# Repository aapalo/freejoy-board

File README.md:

# Freejoy input board

Features:
- Inputs for eg two encoders, eight axes and six shift registers
- Several boards can be daisy-chained via the 1x5 pin socket J103.
- Meant to be used with the Freejoy software: <https://github.com/FreeJoy-Team/FreeJoy>
----

The required components include:
- STM32F103 "Blue Pill"
- Shift register, 74HC165N, DIP-16
- SMD resistors, 10k Ohm, 0805
- SMD capacitors, 470nF, 0805
- Pin sockets and/or headers, 2.54mm pitch
- Buttons/switches
- Jumper wires for the buttons/switches

----

[//]: # (Todo: add pictures of a soldered version)

The schematic (see also pics/schema.pdf):

Top side, with the 3d view and layout view:

Bottom side, with the 3d view and layout view:

Both the top and bottom layer visible:

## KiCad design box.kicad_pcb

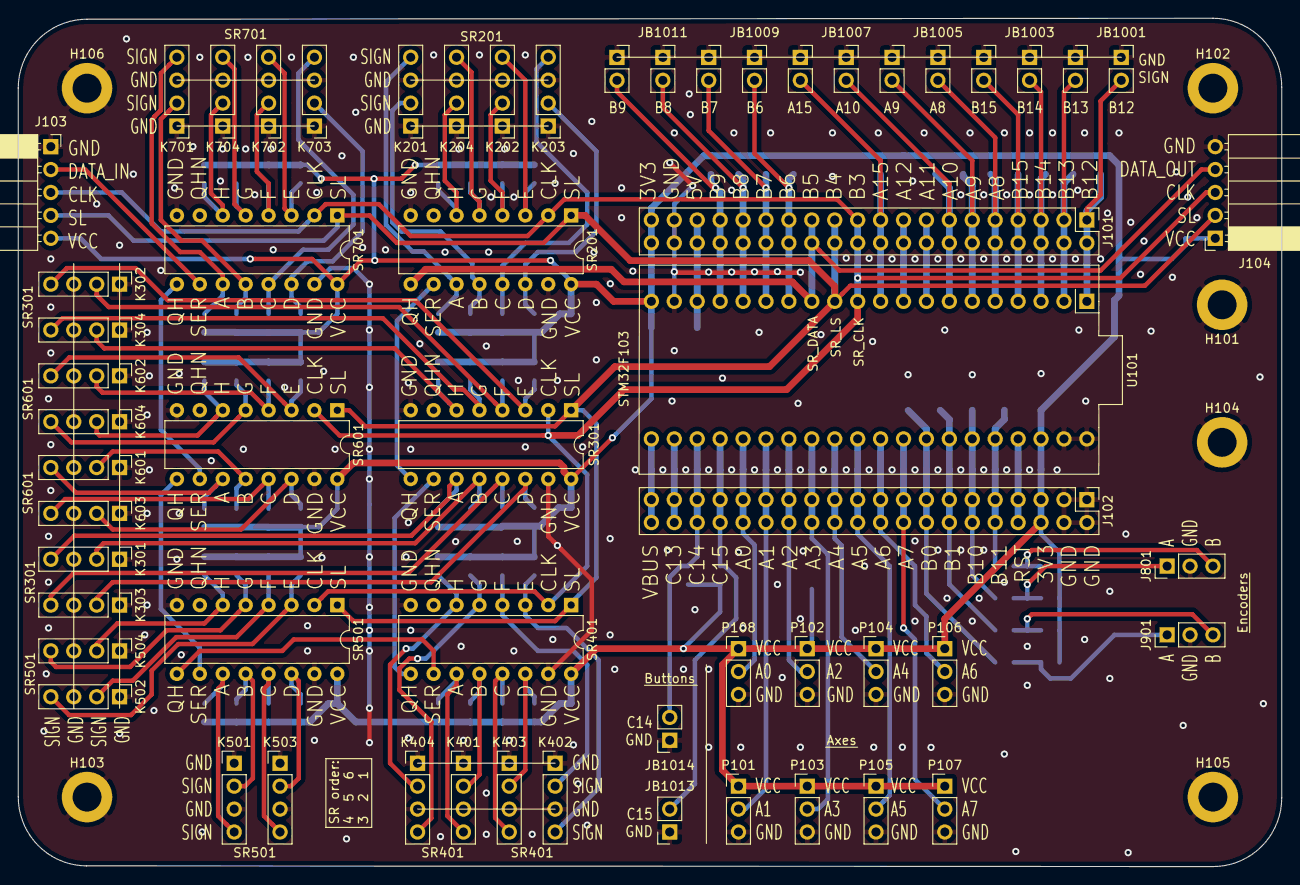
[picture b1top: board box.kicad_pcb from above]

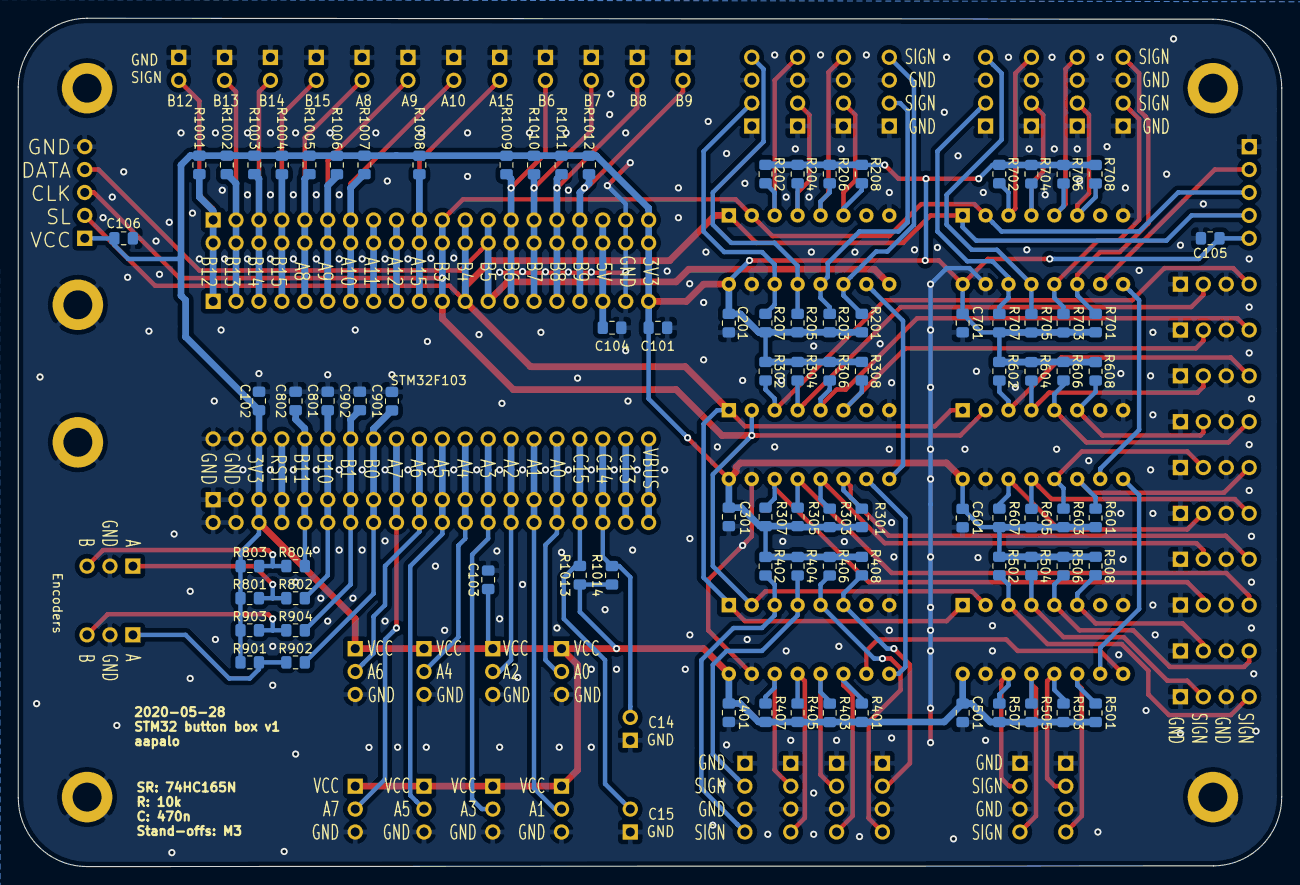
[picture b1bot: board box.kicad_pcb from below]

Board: 2 copper layers, 140.0 x 94.0 mm, 151 parts (86 on the bottom side), 95 nets.

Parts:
C101, C102, C103, C104, C105, C106, C201, C301, C401, C501, C601, C701: 470n; C_0805_2012Metric_Pad1.15x1.40mm_HandSolder
C801, C802, C901, C902: 10n; C_0805_2012Metric_Pad1.15x1.40mm_HandSolder
H101, H102, H103, H104, H105, H106: MountingHole_Pad; MountingHole_3.2mm_M3_DIN965_Pad
J101, J102: Connector_Generic:Conn_02x20_Odd_Even; PinHeader_2x20_P2.54mm_Vertical
J103, J104: Conn_01x05; PinSocket_1x05_P2.54mm_Horizontal
J801, J901: Conn_01x03; PinHeader_1x03_P2.54mm_Vertical
JB1001, JB1002, JB1003, JB1004, JB1005, JB1006, JB1007, JB1008, JB1009, JB1010, JB1011, JB1012, JB1013, JB1014: Conn_01x02; PinSocket_1x02_P2.54mm_Vertical
K201, K202, K203, K204, K301, K302, K303, K304, K401, K402, K403, K404, K501, K502, K503, K504, K601, K602, K603, K604, K701, K702, K703, K704: Conn_01x04; PinHeader_1x04_P2.54mm_Vertical
P101, P102, P103, P104, P105, P106, P107, P108: Conn_01x03_Male; PinHeader_1x03_P2.54mm_Vertical
R201, R202, R203, R204, R205, R206, R207, R208, R301, R302, R303, R304, R305, R306, R307, R308, R401, R402, R403, R404, R405, R406, R407, R408, R501, R502, R503, R504, R505, R506, R507, R508, R601, R602, R603, R604, R605, R606, R607, R608, R701, R702, R703, R704, R705, R706, R707, R708, R801, R802, R803, R804, R901, R902, R903, R904, R1001, R1002, R1003, R1004, R1005, R1006, R1007, R1008, R1009, R1010, R1011, R1012, R1013, R1014: 10k; R_0805_2012Metric_Pad1.15x1.40mm_HandSolder
SR201, SR301, SR401, SR501, SR601, SR701: Conn_02x08_Counter_Clockwise; DIP-16_W7.62mm
U101: Connector_Generic:Conn_02x20_Odd_Even; STM32

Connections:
+3V3: C101.1, C102.1, C103.1, C105.1, C106.1, C201.1, C301.1, C401.1, C501.1, C601.1, C701.1, J101.39, J101.40, J102.5, J102.6, J103.5, J104.1, P101.1, P102.1, P103.1, P104.1, P105.1, P106.1, P107.1, P108.1, R201.2, R202.2, R203.2, R204.2, R205.2, R206.2, R207.2, R208.2, R301.2, R302.2, R303.2, R304.2, R305.2, R306.2, R307.2, R308.2, R401.2, R402.2, R403.2, R404.2, R405.2, R406.2, R407.2, R408.2, R501.2, R502.2, R503.2, R504.2, R505.2, R506.2, R507.2, R508.2, R601.2, R602.2, R603.2, R604.2, R605.2, R606.2, R607.2, R608.2, R701.2, R702.2, R703.2, R704.2, R705.2, R706.2, R707.2, R708.2, R801.1, R803.1, R901.1, R903.1, R1001.1, R1002.1, R1003.1, R1004.1, R1005.1, R1006.1, R1007.1, R1008.1, R1009.1, R1010.1, R1011.1, R1012.1, R1013.1, R1014.1, SR201.16, SR301.16, SR401.16, SR501.16, SR601.16, SR701.16, U101.6, U101.39
/5V: C104.1, J101.35, J101.36, U101.35
/A0: J102.31, J102.32, P108.2, U101.32
/A1: J102.29, J102.30, P101.2, U101.30
/A2: J102.27, J102.28, P102.2, U101.28
/A3: J102.25, J102.26, P103.2, U101.26
/A4: J102.23, J102.24, P104.2, U101.24
/A5: J102.21, J102.22, P105.2, U101.22
/A6: J102.19, J102.20, P106.2, U101.20
/A7: J102.17, J102.18, P107.2, U101.18
/A8: J101.9, J101.10, JB1005.2, R1005.2, U101.9
/A9: J101.11, J101.12, JB1006.2, R1006.2, U101.11
/A10: J101.13, J101.14, JB1007.2, R1007.2, U101.13
/A11: J101.15, J101.16, U101.15
/A12: J101.17, J101.18, U101.17
/A15: J101.19, J101.20, JB1008.2, R1008.2, U101.19
/B0: C901.1, J102.15, J102.16, R902.1, U101.16
/B1: C902.1, J102.13, J102.14, R904.1, U101.14
/B3: J101.21, J101.22, J103.3, J104.3, SR201.2, SR301.2, SR401.2, SR501.2, SR601.2, SR701.2, U101.21
/B4: J101.23, J101.24, J103.4, J104.2, SR201.1, SR301.1, SR401.1, SR501.1, SR601.1, SR701.1, U101.23
/B5: J101.25, J101.26, J104.4, SR201.9, U101.25
/B6: J101.27, J101.28, JB1009.2, R1009.2, U101.27
/B7: J101.29, J101.30, JB1010.2, R1010.2, U101.29
/B8: J101.31, J101.32, JB1011.2, R1011.2, U101.31
/B9: J101.33, J101.34, JB1012.2, R1012.2, U101.33
/B10: C801.1, J102.11, J102.12, R802.1, U101.12
/B11: C802.1, J102.9, J102.10, R804.1, U101.10
/B12: J101.1, J101.2, JB1001.2, R1001.2, U101.1
/B13: J101.3, J101.4, JB1002.2, R1002.2, U101.3
/B14: J101.5, J101.6, JB1003.2, R1003.2, U101.5
/B15: J101.7, J101.8, JB1004.2, R1004.2, U101.7
/C13: J102.37, J102.38, U101.38
/C14: J102.35, J102.36, JB1014.2, R1014.2, U101.36
/C15: J102.33, J102.34, JB1013.2, R1013.2, U101.34
/RST: J102.7, J102.8, U101.8
/SR_DATA_2: SR201.10, SR301.9
/SR_DATA_3: SR301.10, SR401.9
/SR_DATA_4: SR401.10, SR501.9
/SR_DATA_5: SR501.10, SR601.9
/SR_DATA_6: SR601.10, SR701.9
/SR_SER2: J103.2, SR701.10
/Shift register 2/A: K301.4, R301.1, SR301.11
/Shift register 2/B: K301.2, R303.1, SR301.12
/Shift register 2/C: K303.4, R305.1, SR301.13
/Shift register 2/D: K303.2, R307.1, SR301.14
/Shift register 2/E: K302.4, R302.1, SR301.3
/Shift register 2/F: K302.2, R304.1, SR301.4
/Shift register 2/G: K304.4, R306.1, SR301.5
/Shift register 2/H: K304.2, R308.1, SR301.6
/Shift register 3/A: K401.4, R401.1, SR401.11
/Shift register 3/B: K401.2, R403.1, SR401.12
/Shift register 3/C: K403.4, R405.1, SR401.13
/Shift register 3/D: K403.2, R407.1, SR401.14
/Shift register 3/E: K402.4, R402.1, SR401.3
/Shift register 3/F: K402.2, R404.1, SR401.4
/Shift register 3/G: K404.4, R406.1, SR401.5
/Shift register 3/H: K404.2, R408.1, SR401.6
/Shift register 4/A: K501.4, R501.1, SR501.11
/Shift register 4/B: K501.2, R503.1, SR501.12
/Shift register 4/C: K503.4, R505.1, SR501.13
/Shift register 4/D: K503.2, R507.1, SR501.14
/Shift register 4/E: K502.4, R502.1, SR501.3
/Shift register 4/F: K502.2, R504.1, SR501.4
/Shift register 4/G: K504.4, R506.1, SR501.5
/Shift register 4/H: K504.2, R508.1, SR501.6
/Shift register 5/A: K601.4, R601.1, SR601.11
/Shift register 5/B: K601.2, R603.1, SR601.12
/Shift register 5/C: K603.4, R605.1, SR601.13
/Shift register 5/D: K603.2, R607.1, SR601.14
/Shift register 5/E: K602.4, R602.1, SR601.3
/Shift register 5/F: K602.2, R604.1, SR601.4
/Shift register 5/G: K604.4, R606.1, SR601.5
/Shift register 5/H: K604.2, R608.1, SR601.6
/Shift register 6/A: K701.4, R701.1, SR701.11
/Shift register 6/B: K701.2, R703.1, SR701.12
/Shift register 6/C: K703.4, R705.1, SR701.13
/Shift register 6/D: K703.2, R707.1, SR701.14
/Shift register 6/E: K702.4, R702.1, SR701.3
/Shift register 6/F: K702.2, R704.1, SR701.4
/Shift register 6/G: K704.4, R706.1, SR701.5
/Shift register 6/H: K704.2, R708.1, SR701.6
/Shift register/A: K201.4, R201.1, SR201.11
/Shift register/B: K201.2, R203.1, SR201.12
/Shift register/C: K203.4, R205.1, SR201.13
/Shift register/D: K203.2, R207.1, SR201.14
/Shift register/E: K202.4, R202.1, SR201.3
/Shift register/F: K202.2, R204.1, SR201.4
/Shift register/G: K204.4, R206.1, SR201.5
/Shift register/H: K204.2, R208.1, SR201.6
/VBUS: J102.39, J102.40, U101.40
GND: C101.2, C102.2, C103.2, C104.2, C105.2, C106.2, C201.2, C301.2, C401.2, C501.2, C601.2, C701.2, C801.2, C802.2, C901.2, C902.2, H101.1, H102.1, H103.1, H104.1, H105.1, H106.1, J101.37, J101.38, J102.1, J102.2, J102.3, J102.4, J103.1, J104.5, J801.2, J901.2, JB1001.1, JB1002.1, JB1003.1, JB1004.1, JB1005.1, JB1006.1, JB1007.1, JB1008.1, JB1009.1, JB1010.1, JB1011.1, JB1012.1, JB1013.1, JB1014.1, K201.1, K201.3, K202.1, K202.3, K203.1, K203.3, K204.1, K204.3, K301.1, K301.3, K302.1, K302.3, K303.1, K303.3, K304.1, K304.3, K401.1, K401.3, K402.1, K402.3, K403.1, K403.3, K404.1, K404.3, K501.1, K501.3, K502.1, K502.3, K503.1, K503.3, K504.1, K504.3, K601.1, K601.3, K602.1, K602.3, K603.1, K603.3, K604.1, K604.3, K701.1, K701.3, K702.1, K702.3, K703.1, K703.3, K704.1, K704.3, P101.3, P102.3, P103.3, P104.3, P105.3, P106.3, P107.3, P108.3, SR201.8, SR201.15, SR301.8, SR301.15, SR401.8, SR401.15, SR501.8, SR501.15, SR601.8, SR601.15, SR701.8, SR701.15, U101.2, U101.4, U101.37
unnamed: J801.1, R801.2, R802.2
unnamed: J801.3, R803.2, R804.2
unnamed: J901.1, R901.2, R902.2
unnamed: J901.3, R903.2, R904.2

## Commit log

2020-05-25 Initial release
    Initial release
2020-05-25 New layout
    Moved connectors to edges, shrunk board size from 14x14 cm to 14x9 cm.
2020-05-28 First version released
